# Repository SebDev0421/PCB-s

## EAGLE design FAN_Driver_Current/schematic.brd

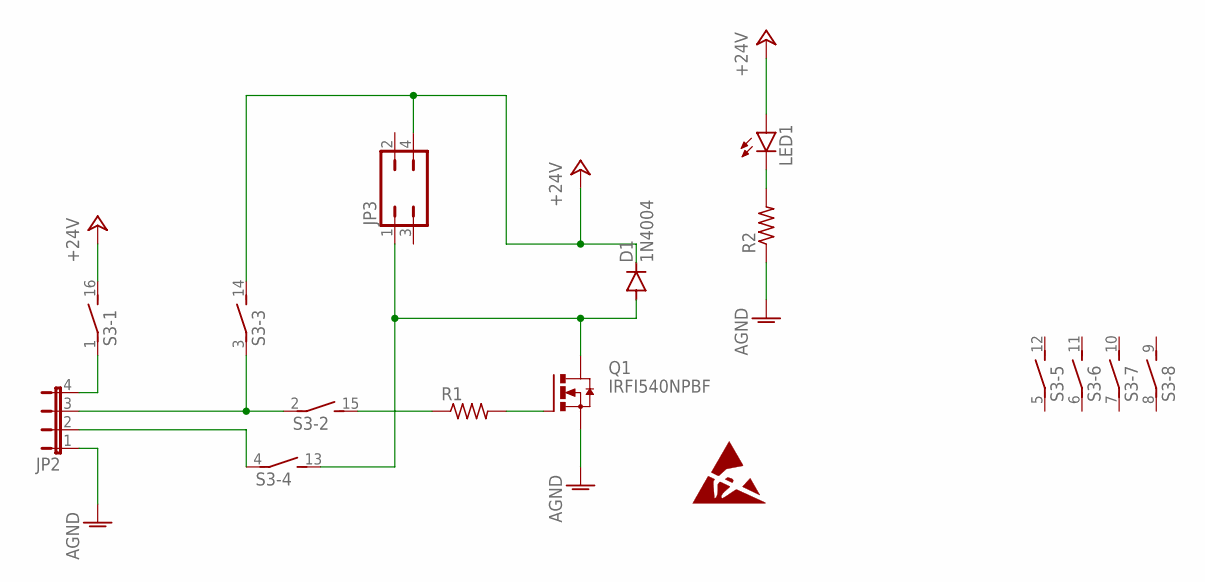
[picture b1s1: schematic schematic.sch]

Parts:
D1: 1N4004; DO41-10
JP2: JP4E; JP4
JP3: JP2Q
LED1: LED3MM
Q1: IRFI540NPBF; TO220BH
R1: R-US_M0805; M0805
R2: R-US_0411/15; 0411/15
S3: DIP08S

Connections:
+24V: D1.C, JP3.4, LED1.A, S3.14 (2), S3.16 (2)
AGND: JP2.1, Q1.S, R2.1
unnamed: Q1.G, R1.2
unnamed: D1.A, JP3.1, Q1.D, S3.13 (2)
unnamed: JP2.3, S3.2 (1), S3.3 (1)
unnamed: JP2.4, S3.1
unnamed: R1.1, S3.15 (2)
unnamed: JP2.2, S3.4 (1)
unnamed: LED1.K (C), R2.2

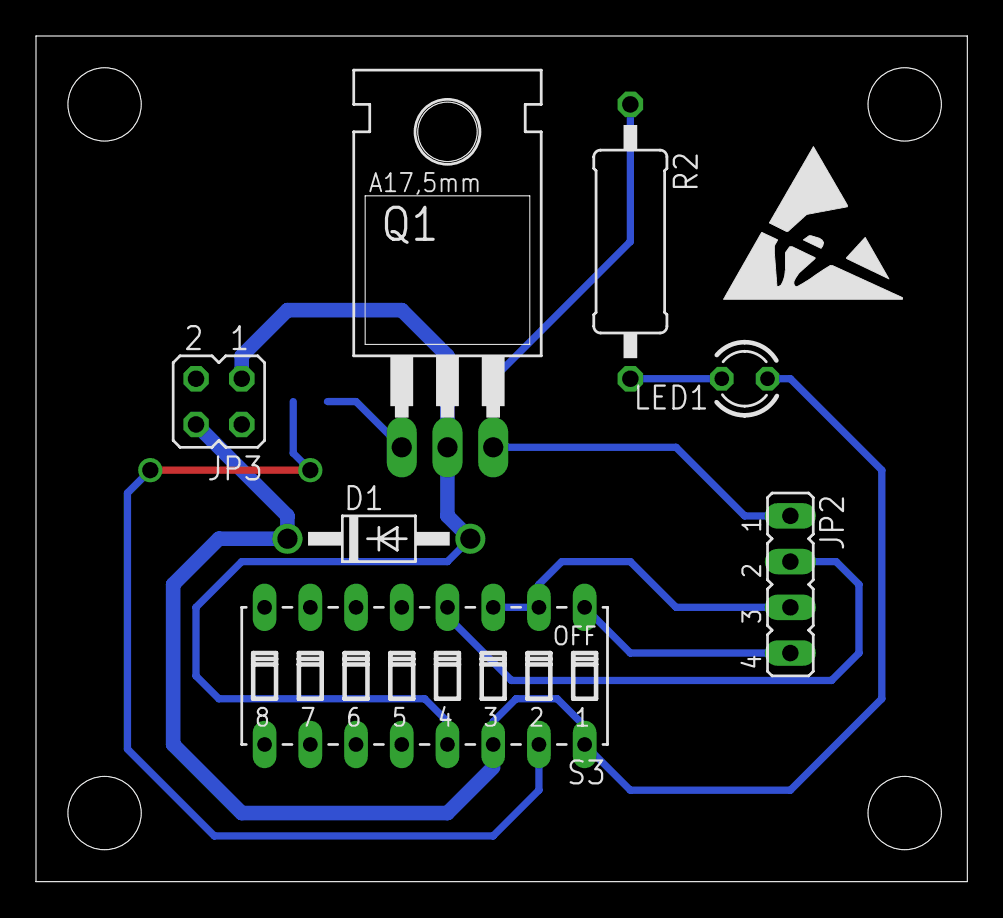
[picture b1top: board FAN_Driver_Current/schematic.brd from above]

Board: 2 copper layers, 51.7 x 47.0 mm, 9 parts (1 on the bottom side), 9 nets.

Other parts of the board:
U$1: ESD_10.00

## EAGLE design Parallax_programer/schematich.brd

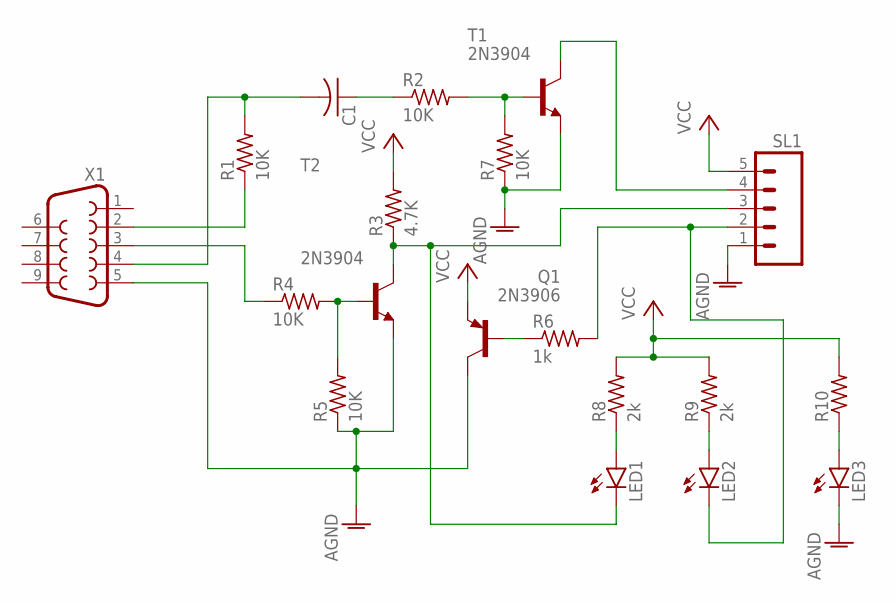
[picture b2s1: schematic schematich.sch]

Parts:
C1: C-USC0805; C0805
LED1, LED2, LED3: LED3MM
Q1: 2N3906; TO92
R1, R2, R4, R5, R7: 10K; M1406
R3: 4.7K; M1406
R6: 1k; M1406
R8, R9: 2k; M0805
R10: R-US_M0805; M0805
SL1: M05; 05P
T1, T2: 2N3904; TO92
X1: F09HP

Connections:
AGND: LED3.K (C), Q1.1 (C), R5.1, R7.1, SL1.1, T1.3 (E), T2.3 (E), X1.5
unnamed: R1.1, X1.2
unnamed: C1.2, R1.2, X1.4
unnamed: C1.1, R2.1
unnamed: R2.2, R7.2, T1.2 (B)
unnamed: Q1.2 (B), R6.1
unnamed: R4.2, R5.2, T2.2 (B)
unnamed: R4.1, X1.3
unnamed: LED1.K (C), R3.1, SL1.3, T2.1 (C)
unnamed: LED2.K (C), R6.2, SL1.2
unnamed: SL1.4, T1.1 (C)
unnamed: LED1.A, R8.1
unnamed: LED2.A, R9.1
unnamed: LED3.A, R10.1
VCC: Q1.3 (E), R3.2, R8.2, R9.2, R10.2, SL1.5

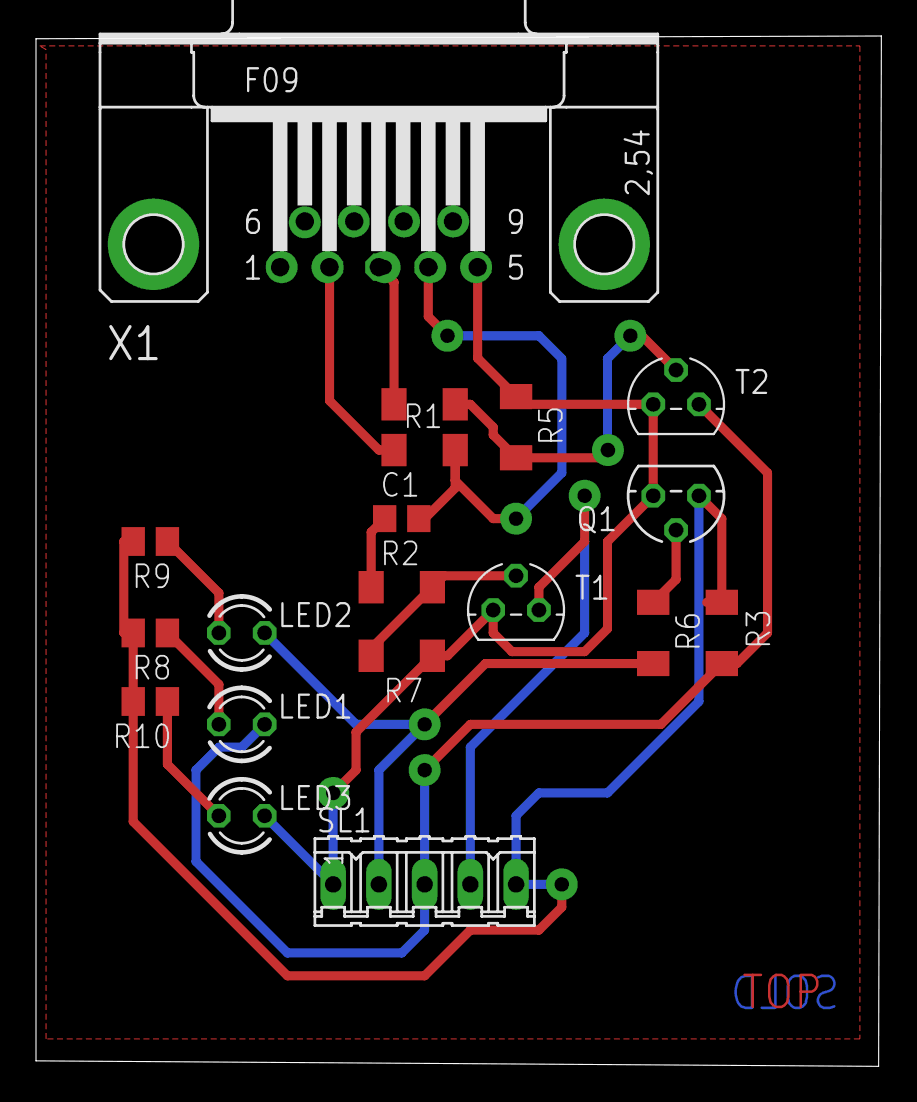
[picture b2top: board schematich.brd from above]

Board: 2 copper layers, 47.0 x 57.2 mm, 19 parts (0 on the bottom side), 15 nets.

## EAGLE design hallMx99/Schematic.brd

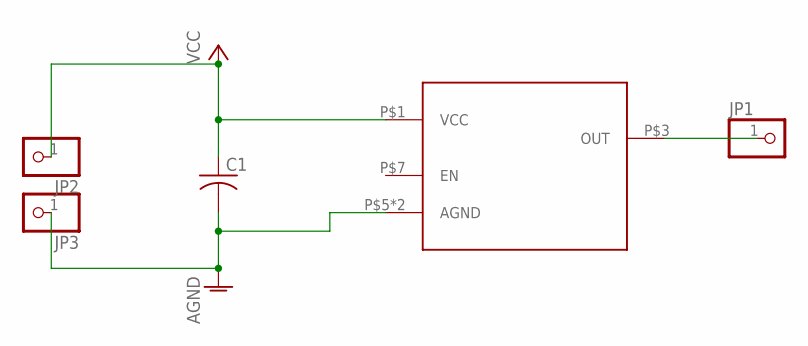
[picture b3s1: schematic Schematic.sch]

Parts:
C1: C-USC0805; C0805
JP1, JP2, JP3: PINHD-1X1; 1X01
U$1: MLX92213

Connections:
AGND: C1.2, JP3.1, U$1.P$5 (AGND), U$1.P$8 (AGND)
unnamed: JP1.1, U$1.P$3 (OUT)
VCC: C1.1, JP2.1, U$1.P$1 (VCC)

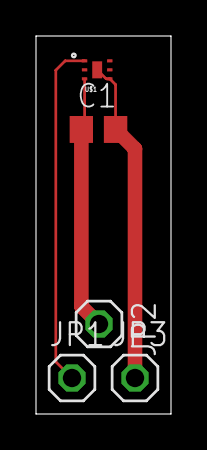
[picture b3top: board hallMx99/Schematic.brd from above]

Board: 2 copper layers, 7.5 x 21.0 mm, 5 parts (0 on the bottom side), 3 nets.

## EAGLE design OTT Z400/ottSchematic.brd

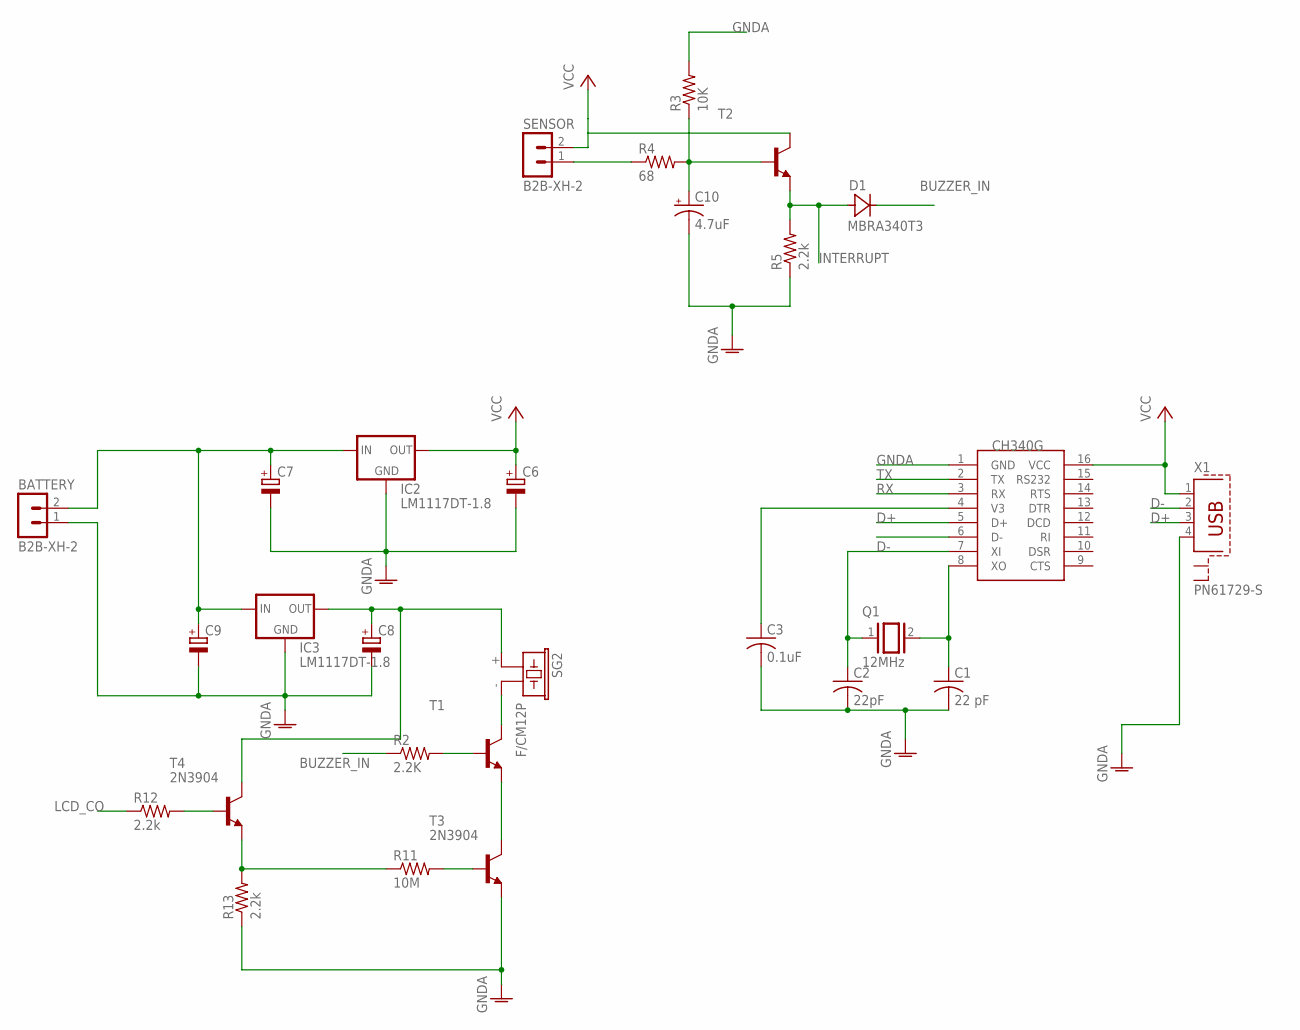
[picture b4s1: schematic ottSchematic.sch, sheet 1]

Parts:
BATTERY: B2B-XH-2; B2B-XH-A
C1: 22 pF; C0603K
C2: 22pF; C0603K
C3: 0.1uF; C1206K
C6, C7, C8, C9: CPOL-EU175TMP-0808; 175TMP-0808
C10: 4.7uF; E5-8,5
D1: MBRA340T3; SMA
IC2, IC3: LM1117DT-1.8; TO252
Q1: 12MHz; QS
R2: 2.2K; R0805
R3: 10K; R0805
R4: 68; 0309/12
R5, R12, R13: 2.2k; R0805
R11: 10M; R0805
SENSOR: B2B-XH-2; B2B-XH-A
SG2: F/CM12P
T1, T2: MMBT3904LT1-NPN-SOT23-BEC; SOT23-BEC
T3, T4: 2N3904; TO92
U$1: CH340G; SOIC16
X1: PN61729-S

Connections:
BUZZER_IN: D1.C, R2.1; also elsewhere on the board
D+: U$1.5 (D+), X1.3
D-: U$1.6 (D-), X1.2
GNDA: BATTERY.1, C1.2, C2.2, C3.2, C6.-, C7.-, C8.-, C9.-, C10.-, IC2.1 (GND), IC3.1 (GND), R3.2, R5.1, R13.1, T3.3 (E), U$1.1 (GND), X1.4; also elsewhere on the board
INTERRUPT: D1.A, R5.2, T2.E; also elsewhere on the board
LCD_CO: R12.1; also elsewhere on the board
unnamed: C1.1, Q1.2, U$1.8 (XO)
unnamed: C2.1, Q1.1, U$1.7 (XI)
unnamed: C3.1, U$1.4 (V3)
unnamed: SG2.- (2), T1.C
unnamed: C10.+, R3.1, R4.2, T2.B
unnamed: BATTERY.2, C7.+, C9.+, IC2.2 (IN), IC3.2 (IN)
unnamed: C8.+, IC3.3 (OUT), SG2.+ (1), T4.1 (C)
unnamed: R4.1, SENSOR.1
unnamed: T1.E, T3.1 (C)
unnamed: R2.2, T1.B
unnamed: R11.2, T3.2 (B)
unnamed: R11.1, R13.2, T4.3 (E)
unnamed: R12.2, T4.2 (B)
RX: U$1.3 (RX); also elsewhere on the board
TX: U$1.2 (TX); also elsewhere on the board
VCC: C6.+, IC2.3 (OUT), SENSOR.2, T2.C, U$1.16 (VCC), X1.1; also elsewhere on the board

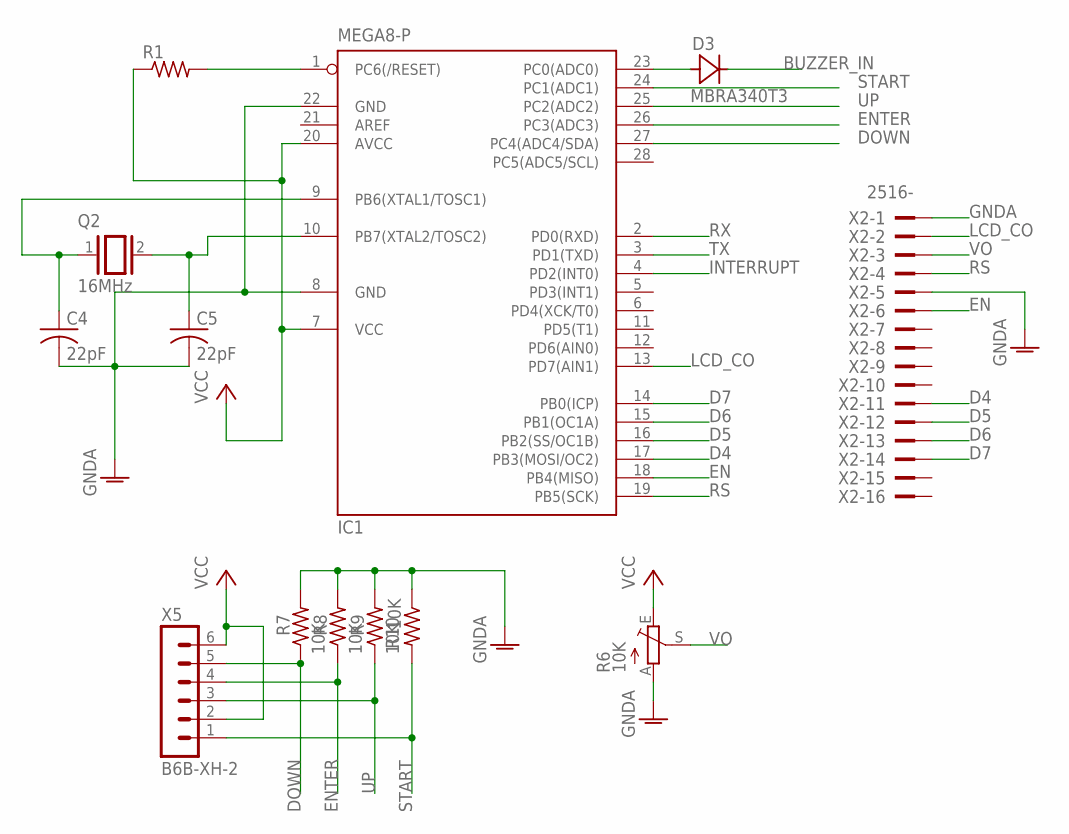
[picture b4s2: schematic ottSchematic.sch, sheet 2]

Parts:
C4, C5: 22pF; C0805
D3: MBRA340T3; SMA
IC1: MEGA8-P; DIL28-3
Q2: 16MHz; QS
R1: R-US_R0805; R0805
R6: 10K; B64Y
R7, R8, R9, R10: 10K; R0805
X2: 2516-; PAK100/2500-16
X5: B6B-XH-2; B6B-XH-A

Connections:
BUZZER_IN: D3.C; also elsewhere on the board
D4: IC1.17 (PB3(MOSI/OC2)), X2.11
D5: IC1.16 (PB2(SS/OC1B)), X2.12
D6: IC1.15 (PB1(OC1A)), X2.13
D7: IC1.14 (PB0(ICP)), X2.14
DOWN: IC1.27 (PC4(ADC4/SDA)), R7.1, X5.5
EN: IC1.18 (PB4(MISO)), X2.6
ENTER: IC1.26 (PC3(ADC3)), R8.1, X5.4
GNDA: C4.2, C5.2, IC1.8 (GND), IC1.22 (GND), R6.A, R7.2, R8.2, R9.2, R10.1, X2.1, X2.5; also elsewhere on the board
INTERRUPT: IC1.4 (PD2(INT0)); also elsewhere on the board
LCD_CO: IC1.13 (PD7(AIN1)), X2.2; also elsewhere on the board
unnamed: C4.1, IC1.9 (PB6(XTAL1/TOSC1)), Q2.1
unnamed: C5.1, IC1.10 (PB7(XTAL2/TOSC2)), Q2.2
unnamed: IC1.1 (PC6(/RESET)), R1.2
unnamed: D3.A, IC1.23 (PC0(ADC0))
RS: IC1.19 (PB5(SCK)), X2.4
RX: IC1.2 (PD0(RXD)); also elsewhere on the board
START: IC1.24 (PC1(ADC1)), R10.2, X5.1
TX: IC1.3 (PD1(TXD)); also elsewhere on the board
UP: IC1.25 (PC2(ADC2)), R9.1, X5.3
VCC: IC1.7 (VCC), IC1.20 (AVCC), R1.1, R6.E, X5.2, X5.6; also elsewhere on the board
VO: R6.S, X2.3

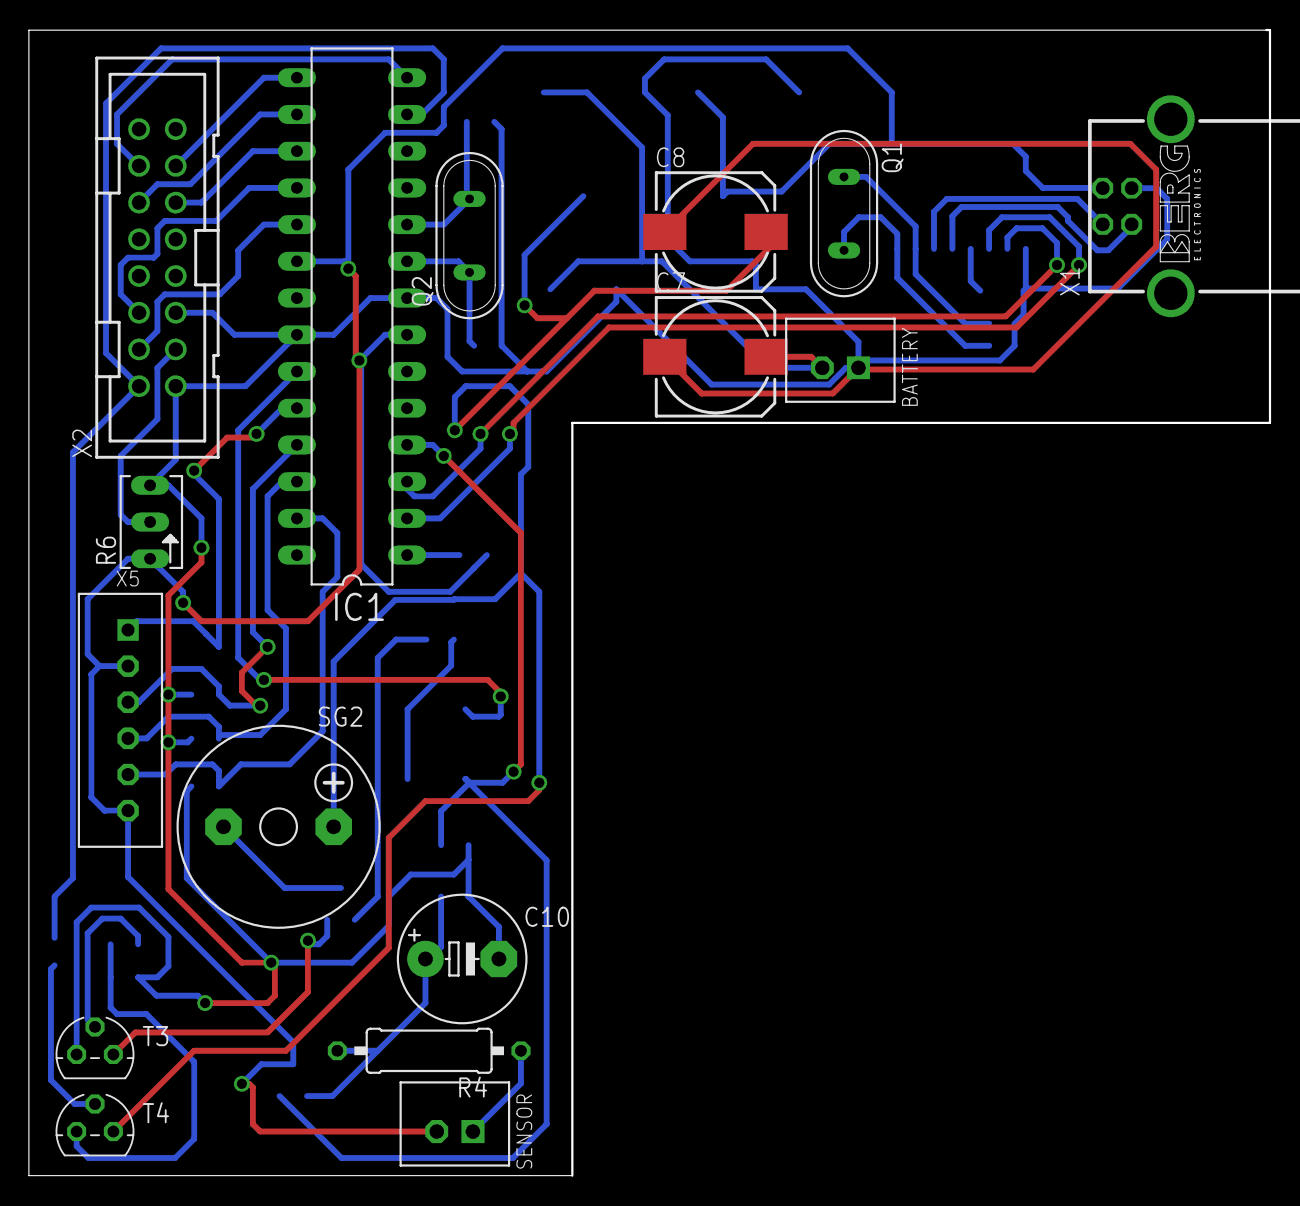
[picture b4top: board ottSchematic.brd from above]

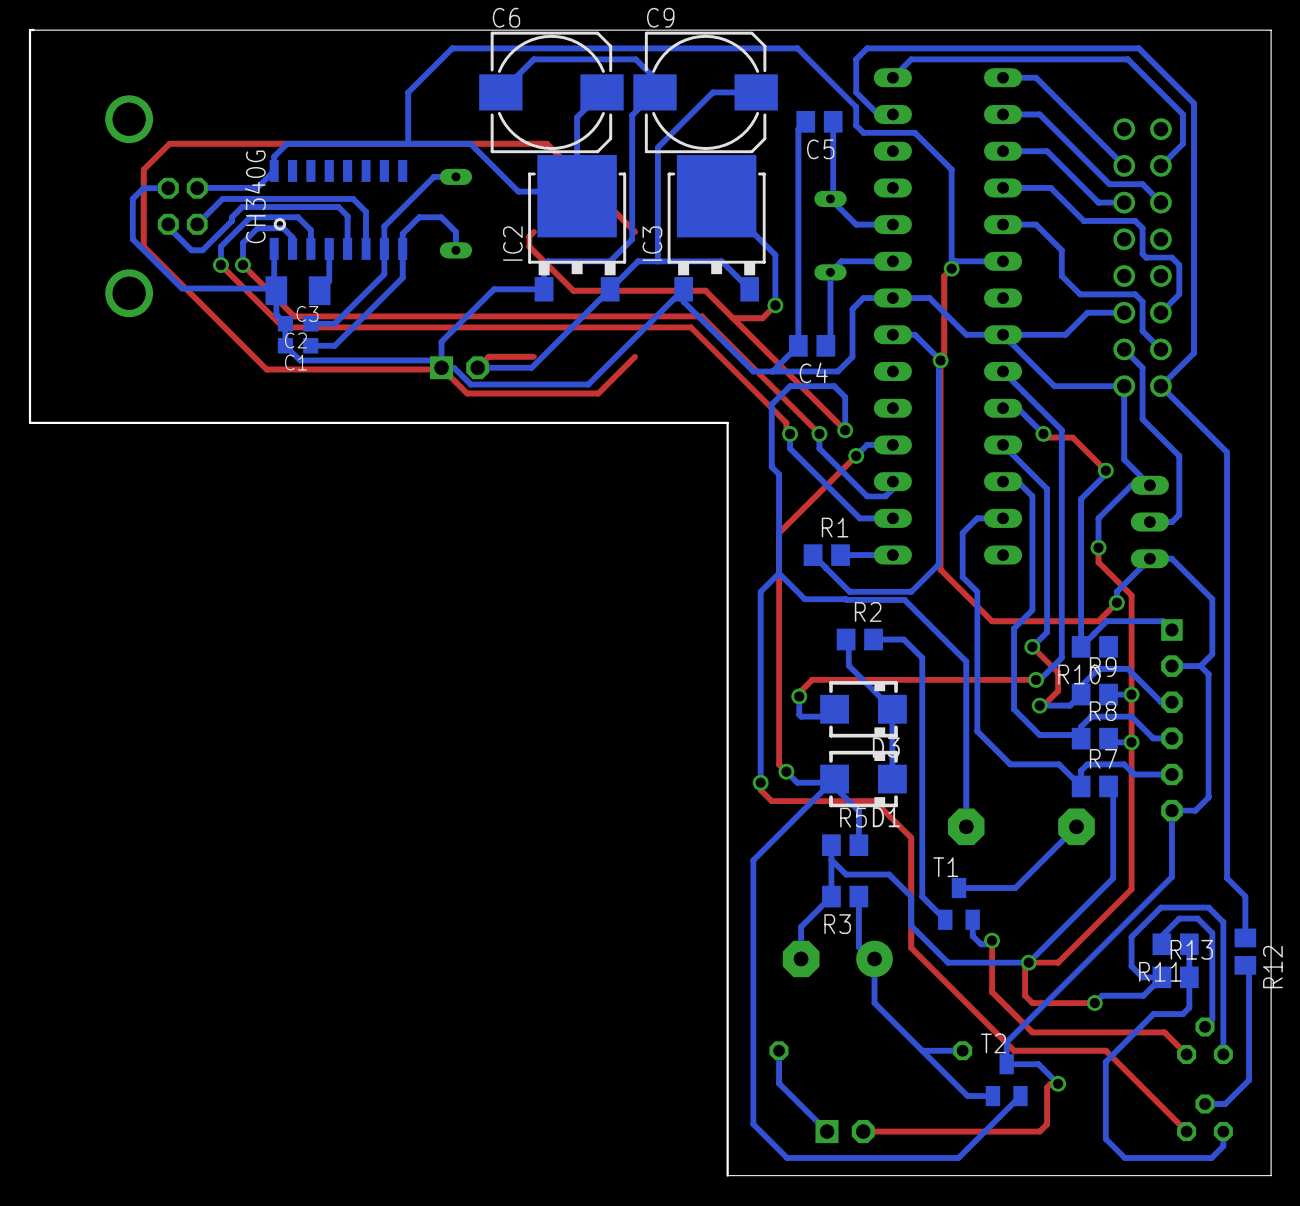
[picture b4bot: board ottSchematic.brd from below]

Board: 2 copper layers, 85.8 x 79.2 mm, 41 parts (25 on the bottom side), 37 nets.

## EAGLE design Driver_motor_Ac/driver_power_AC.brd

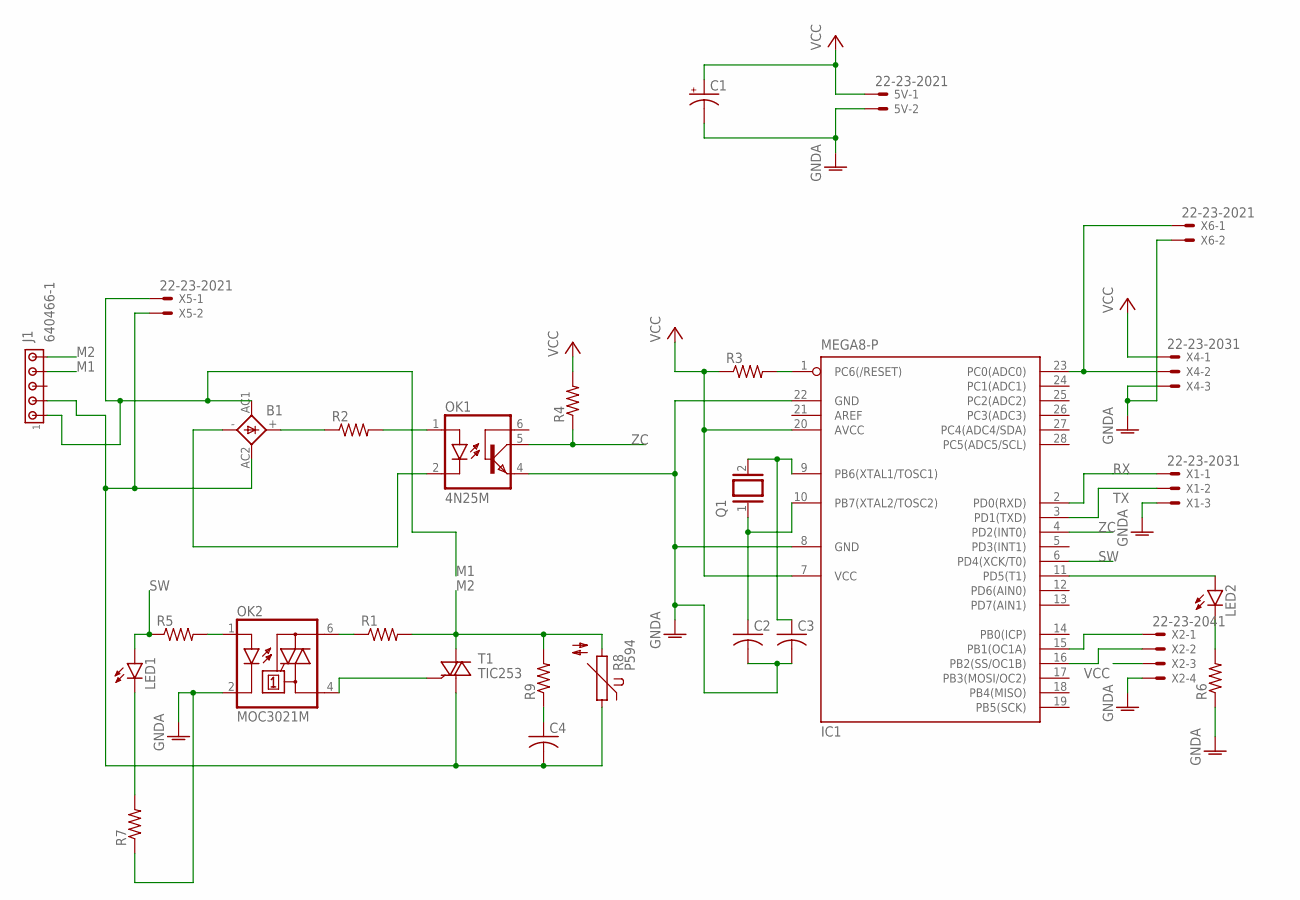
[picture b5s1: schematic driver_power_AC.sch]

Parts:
5V: 22-23-2021
B1: SKB
C1: CPOL-USE5-10.5; E5-10,5
C2, C3: C-US025-025X050; C025-025X050
C4: C-US050-025X075; C050-025X075
IC1: MEGA8-P; DIL28-3
J1: 640466-1
LED1, LED2: LED3MM
OK1: 4N25M; DIL06
OK2: MOC3021M; DIL06
Q1: XTAL/S; QS
R1: R-US_0411/12; 0411/12
R2: R-US_0617/22; 0617/22
R3: R-US_0204/7; 0204/7
R4, R5, R6, R7: R-US_0207/10; 0207/10
R8: P594
R9: R-US_0207/7; 0207/7
T1: TIC253; TO218DS
X1, X4: 22-23-2031
X2: 22-23-2041
X5, X6: 22-23-2021

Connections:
GNDA: 5V.2, C1.-, C2.2, C3.2, IC1.8 (GND), IC1.22 (GND), OK1.4 (EMI), OK2.2 (C), R6.1, R7.1, X1.3, X2.4, X4.3, X6.2
M1: B1.AC1, J1.1, J1.4, X5.1
M2: J1.5, R1.2, R8.2, R9.2, T1.A2
unnamed: IC1.15 (PB1(OC1A)), X2.1
unnamed: OK2.6 (A2), R1.1
unnamed: OK1.1 (A), R2.2
unnamed: OK2.4 (A1), T1.G
unnamed: B1.+, R2.1
unnamed: B1.-, OK1.2 (C)
unnamed: B1.AC2, C4.2, J1.2, R8.1, T1.A1, X5.2
unnamed: IC1.16 (PB2(SS/OC1B)), X2.2
unnamed: IC1.11 (PD5(T1)), LED2.A
unnamed: LED1.K (C), R7.2
unnamed: IC1.1 (PC6(/RESET)), R3.2
unnamed: IC1.23 (PC0(ADC0)), X4.2, X6.1
unnamed: OK2.1 (A), R5.2
unnamed: LED2.K (C), R6.2
unnamed: C3.1, IC1.9 (PB6(XTAL1/TOSC1)), Q1.2
unnamed: C2.1, IC1.10 (PB7(XTAL2/TOSC2)), Q1.1
unnamed: C4.1, R9.1
RX: IC1.2 (PD0(RXD)), X1.1
SW: IC1.6 (PD4(XCK/T0)), LED1.A, R5.1
TX: IC1.3 (PD1(TXD)), X1.2
VCC: 5V.1, C1.+, IC1.7 (VCC), IC1.20 (AVCC), R3.1, R4.2, X2.3, X4.1
ZC: IC1.4 (PD2(INT0)), OK1.5 (COL), R4.1

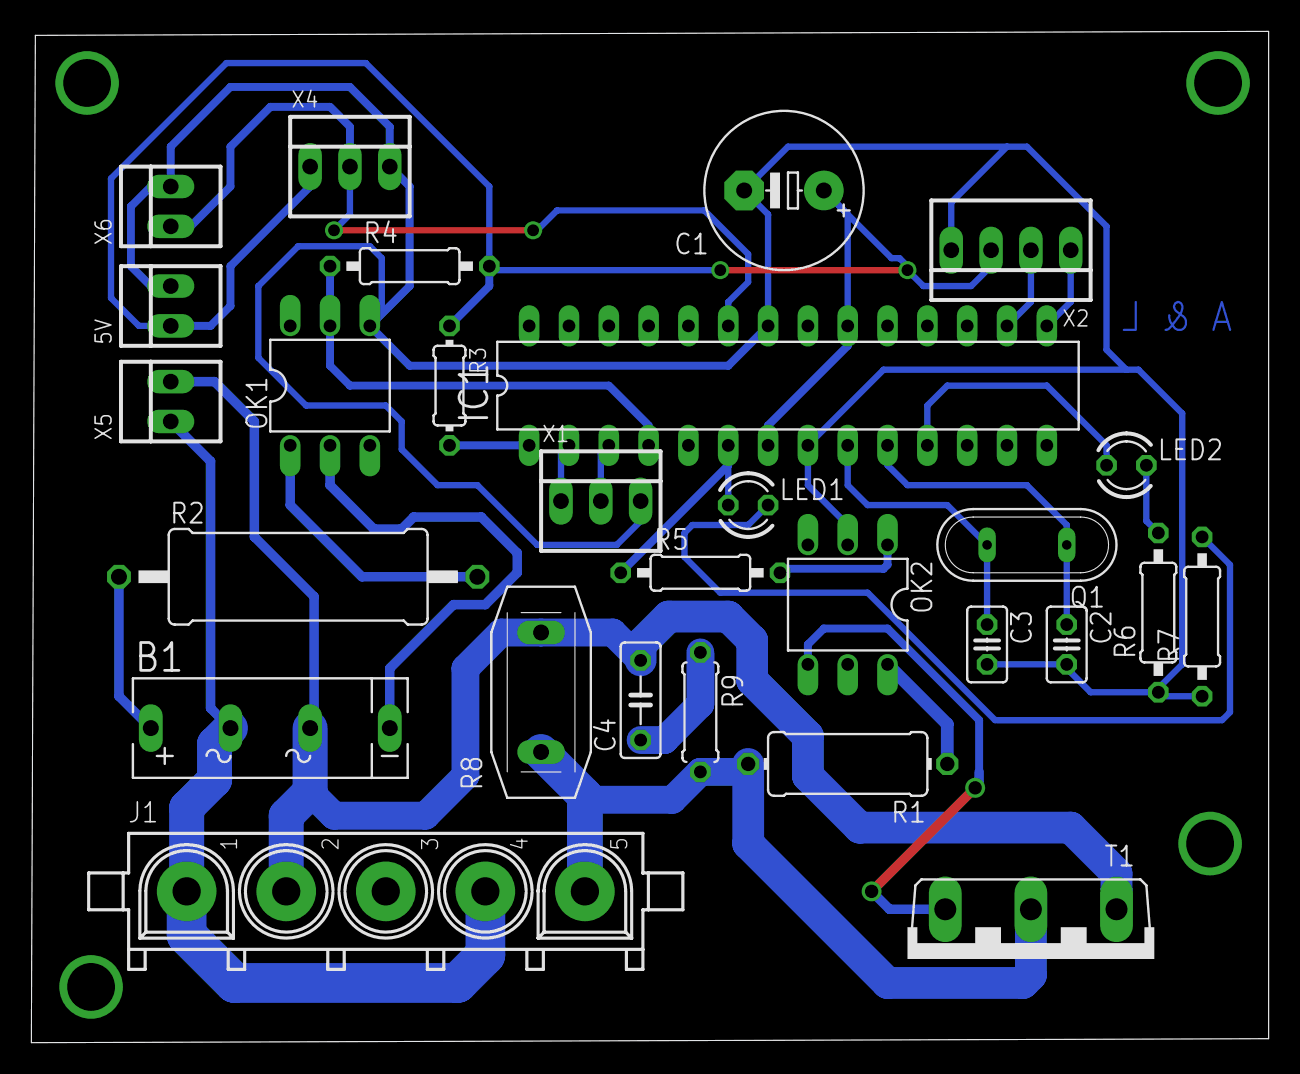
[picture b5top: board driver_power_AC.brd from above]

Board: 2 copper layers, 78.9 x 64.5 mm, 28 parts (0 on the bottom side), 25 nets.

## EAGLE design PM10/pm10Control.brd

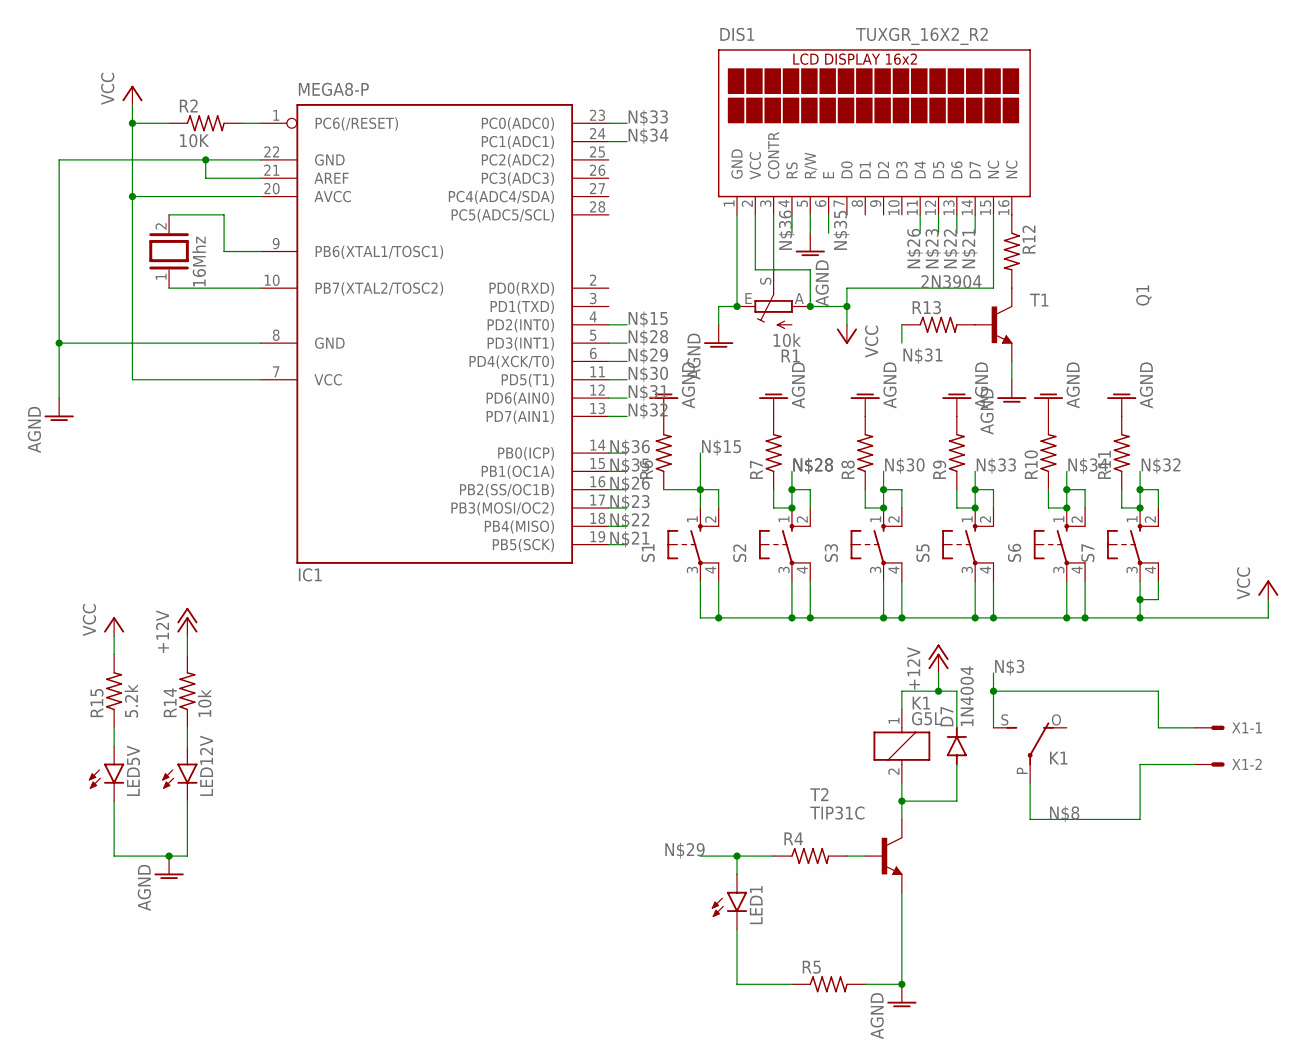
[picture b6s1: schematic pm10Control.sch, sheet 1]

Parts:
D7: 1N4004; DO41-10
DIS1: TUXGR_16X2_R2
IC1: MEGA8-P; DIL28-3
K1: G5L; G5LE
LED1, LED5V, LED12V: LED3MM
Q1: 16Mhz; QS
R1: 10k; B64Y
R2: 10K; 0207/10
R4, R5, R6, R7, R8, R9, R10, R11, R12, R13: R-US_0207/10; 0207/10
R14: 10k; 0207/10
R15: 5.2k; 0207/10
S1, S2, S3, S5, S6, S7: 10-XX; B3F-10XX
T1: 2N3904; TO92
T2: TIP31C; TO220
X1: KK-156-2

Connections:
+12V: D7.C, K1.1, R14.2; also elsewhere on the board
AGND: DIS1.1 (GND), DIS1.5 (R/W), IC1.8 (GND), IC1.21 (AREF), IC1.22 (GND), LED5V.K (C), LED12V.K (C), R1.E, R5.2, R6.2, R7.2, R8.2, R9.2, R10.2, R11.2, T1.3 (E), T2.3 (E); also elsewhere on the board
unnamed: IC1.9 (PB6(XTAL1/TOSC1)), Q1.2
unnamed: IC1.10 (PB7(XTAL2/TOSC2)), Q1.1
unnamed: K1.S, X1.1
unnamed: DIS1.16 (NC), R12.1
unnamed: R12.2, T1.1 (C)
unnamed: R13.2, T1.2 (B)
unnamed: IC1.1 (PC6(/RESET)), R2.2
unnamed: K1.P, X1.2
unnamed: DIS1.3 (CONTR), R1.S
unnamed: LED5V.A, R15.1
unnamed: LED12V.A, R14.1
unnamed: IC1.4 (PD2(INT0)), R6.1, S1.1 (S), S1.2 (S1)
unnamed: DIS1.14 (D7), IC1.19 (PB5(SCK))
unnamed: DIS1.13 (D6), IC1.18 (PB4(MISO))
unnamed: DIS1.12 (D5), IC1.17 (PB3(MOSI/OC2))
unnamed: D7.A, K1.2, T2.2 (C)
unnamed: R4.2, T2.1 (B)
unnamed: DIS1.11 (D4), IC1.16 (PB2(SS/OC1B))
unnamed: LED1.K (C), R5.1
unnamed: IC1.5 (PD3(INT1)), R7.1, S2.1 (S), S2.2 (S1)
unnamed: IC1.6 (PD4(XCK/T0)), LED1.A, R4.1
unnamed: IC1.11 (PD5(T1)), R8.1, S3.1 (S), S3.2 (S1)
unnamed: IC1.12 (PD6(AIN0)), R13.1
unnamed: IC1.13 (PD7(AIN1)), R11.1, S7.1 (S), S7.2 (S1)
unnamed: IC1.23 (PC0(ADC0)), R9.1, S5.1 (S), S5.2 (S1)
unnamed: IC1.24 (PC1(ADC1)), R10.1, S6.1 (S), S6.2 (S1)
unnamed: DIS1.6 (E), IC1.15 (PB1(OC1A))
unnamed: DIS1.4 (RS), IC1.14 (PB0(ICP))
VCC: DIS1.2 (VCC), DIS1.15 (NC), IC1.7 (VCC), IC1.20 (AVCC), R1.A, R2.1, R15.2, S1.3, S1.4 (P1), S2.3, S2.4 (P1), S3.3, S3.4 (P1), S5.3, S5.4 (P1), S6.3, S6.4 (P1), S7.3, S7.4 (P1); also elsewhere on the board

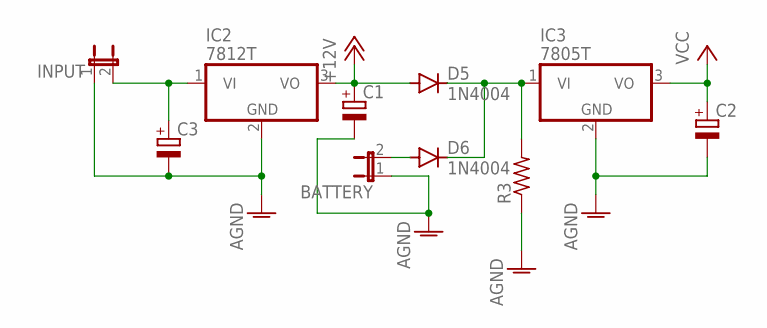
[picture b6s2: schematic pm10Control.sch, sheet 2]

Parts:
BATTERY: JP1E; JP1
C1, C2, C3: CPOL-EUE5-10.5; E5-10,5
D5, D6: 1N4004; DO41-10
IC2: 7812T; TO220H
IC3: 7805T; TO220H
INPUT: JP1E; JP1
R3: R-US_0207/10; 0207/10

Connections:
+12V: C1.+, D5.A, IC2.3 (VO); also elsewhere on the board
AGND: BATTERY.1, C1.-, C2.-, C3.-, IC2.2 (GND), IC3.2 (GND), INPUT.1, R3.1; also elsewhere on the board
unnamed: D5.C, D6.C, IC3.1 (VI), R3.2
unnamed: BATTERY.2, D6.A
unnamed: C3.+, IC2.1 (VI), INPUT.2
VCC: C2.+, IC3.3 (VO); also elsewhere on the board

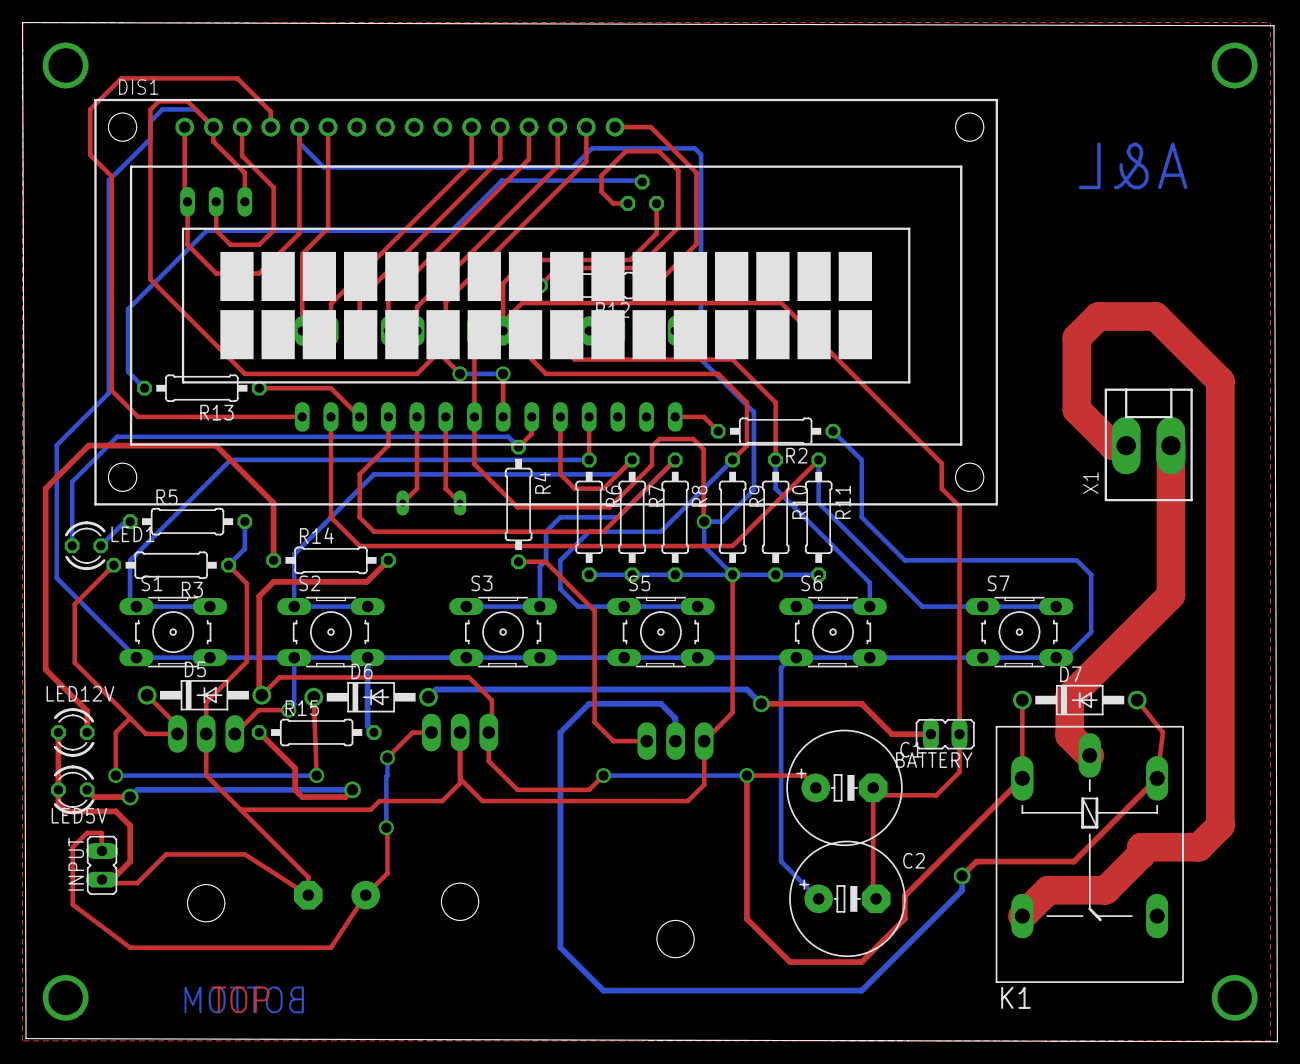
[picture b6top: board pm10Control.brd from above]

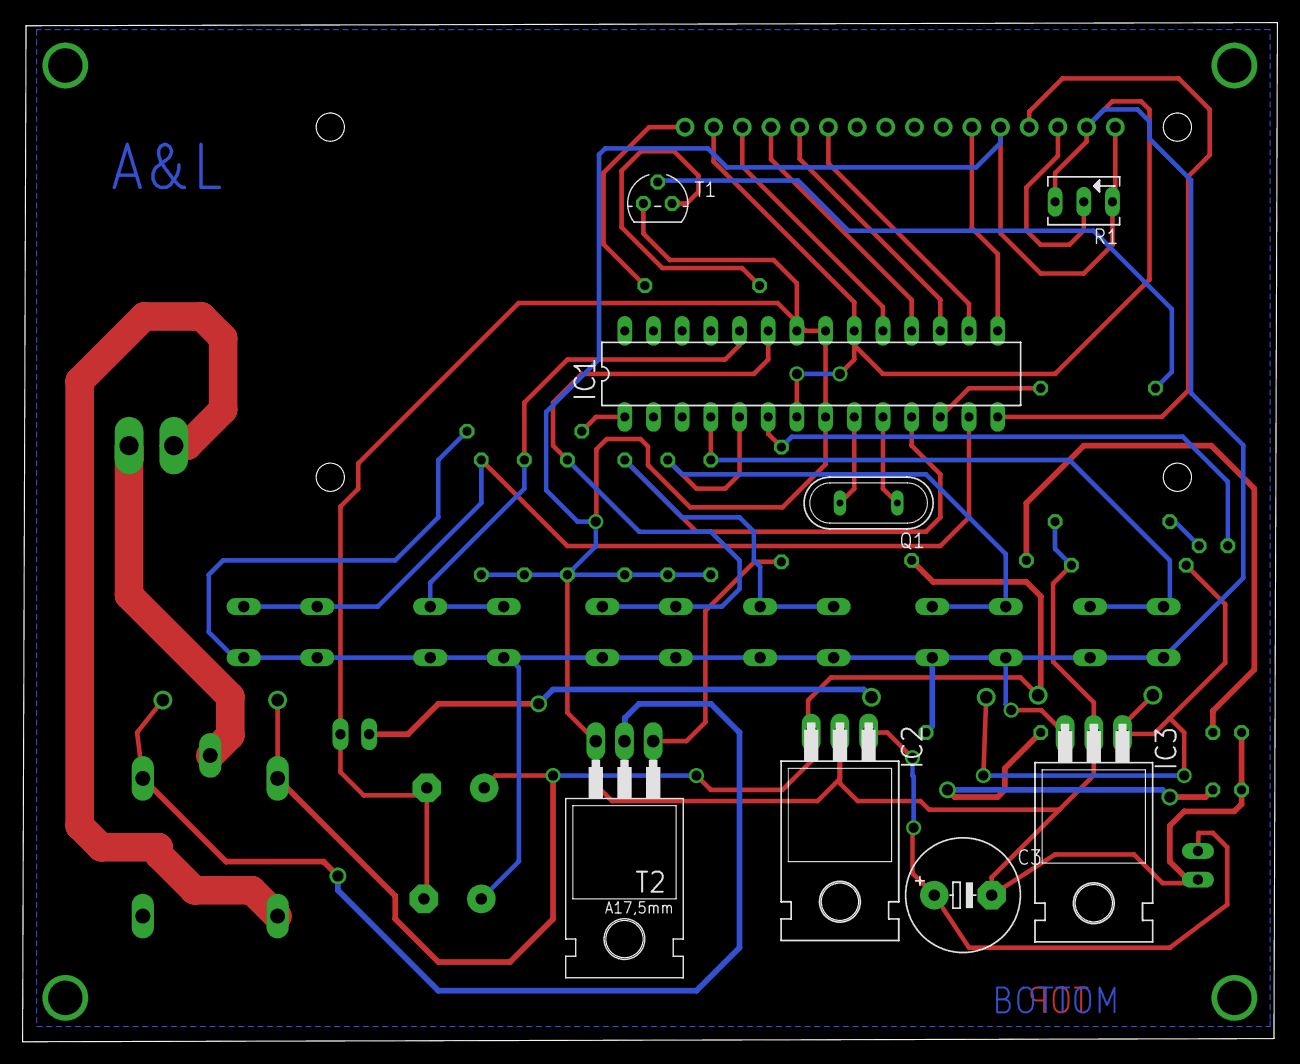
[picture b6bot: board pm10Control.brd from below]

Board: 2 copper layers, 111.1 x 90.2 mm, 41 parts (8 on the bottom side), 34 nets.

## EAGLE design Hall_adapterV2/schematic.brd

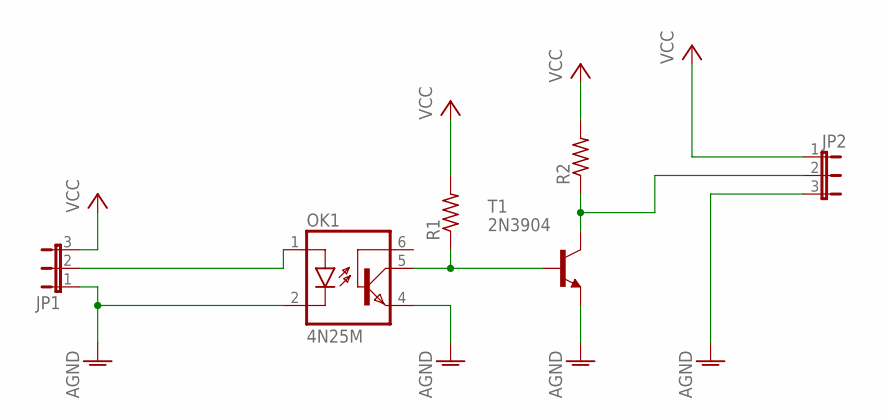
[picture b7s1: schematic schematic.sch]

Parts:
JP1, JP2: JP2E; JP2
OK1: 4N25M; DIL06
R1, R2: R-US_0207/10; 0207/10
T1: 2N3904; TO92

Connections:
AGND: JP1.1, JP2.3, OK1.2 (C), OK1.4 (EMI), T1.3 (E)
unnamed: JP1.2, OK1.1 (A)
unnamed: OK1.5 (COL), R1.1, T1.2 (B)
unnamed: JP2.2, R2.1, T1.1 (C)
VCC: JP1.3, JP2.1, R1.2, R2.2

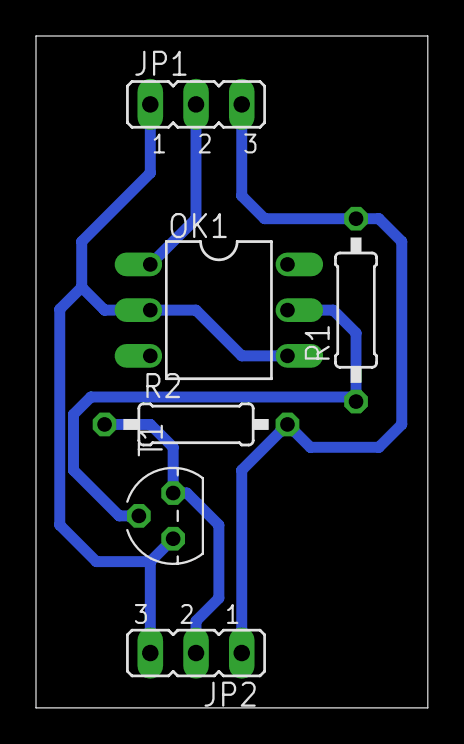
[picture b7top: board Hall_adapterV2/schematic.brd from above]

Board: 2 copper layers, 21.8 x 37.3 mm, 6 parts (0 on the bottom side), 5 nets.

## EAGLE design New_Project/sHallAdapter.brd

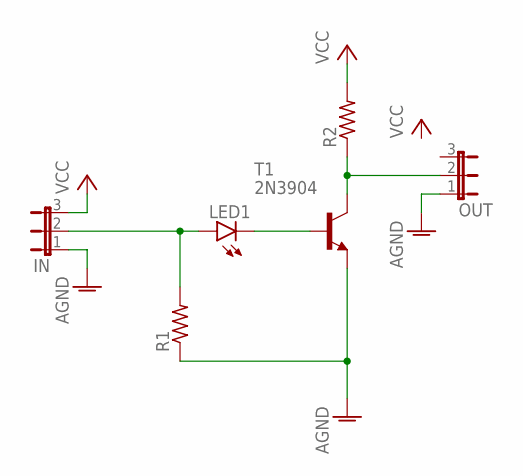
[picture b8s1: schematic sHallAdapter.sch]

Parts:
IN: JP2E; JP2
LED1: LED3MM
OUT: JP2E; JP2
R1, R2: R-US_R0805W; R0805W
T1: 2N3904; TO92

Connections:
AGND: IN.1, OUT.1, R1.1, T1.3 (E)
unnamed: LED1.K (C), T1.2 (B)
unnamed: IN.2, LED1.A, R1.2
unnamed: OUT.2, R2.1, T1.1 (C)
VCC: IN.3, R2.2

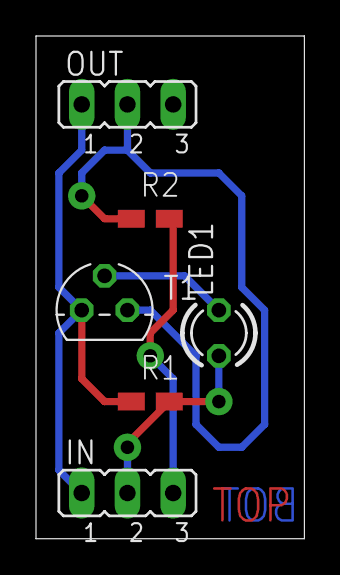
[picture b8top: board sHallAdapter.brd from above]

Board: 2 copper layers, 14.9 x 27.9 mm, 6 parts (0 on the bottom side), 5 nets.

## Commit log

2021-07-02 fisrt commit
